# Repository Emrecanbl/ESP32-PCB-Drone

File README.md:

# Micro-Drone Flight Stack — STM32H743

A custom flight controller for a 3S micro-drone, designed from scratch: schematic, multi-layer PCB, and firmware.
The board is not a carrier for off-the-shelf modules — MCU, sensors, power tree and connectivity are all part of one design.

> **Status:** Rev 1 hardware design complete (KiCad 9). Firmware in development.

---

## 1. What this is

The goal is a **modular flight platform** that starts as a stabilised micro-drone and grows into an autonomous system: optical flow and ToF for indoor hold, GPS for outdoor navigation, and eventually a ROS 2 companion computer for SLAM.

Every stage is built and verified before the next one starts. This repository documents the hardware as designed and the firmware as it comes up.

**Why build the controller instead of using an off-the-shelf FC:** the interesting engineering is in the parts a commercial board hides — the analogue power path under a switching regulator, the sensor bus layout, the real-time task structure, and the failure behaviour when a link drops. Designing the board makes all of that visible and measurable.

---

## 2. Flight controller hardware (Rev 1)

### 2.1 Core

| Item | Part | Notes |
|---|---|---|
| MCU | **STM32H743VIT** | Cortex-M7, LQFP-100 |
| HSE crystal | 13.0625 MHz | with 10 pF load caps |
| LSE crystal | 32.768 kHz | RTC / low-speed domain |
| Debug | SWD/JTAG header (J2) | |
| Console | UART header (J3) | separate from the ESP32 link |
| USB | USB-C receptacle (J9) | USB 2.0 FS, CC1/CC2 with 5.1 kΩ sink resistors |

VCAP decoupling (2× 2.2 µF), bulk + local 100 nF per supply pin, and a **600 Ω ferrite on VDDA** to keep the ADC/analogue reference off the digital rail.

### 2.2 Sensors

| Function | Part | Bus | Notes |
|---|---|---|---|
| IMU | **Bosch BMI088** | SPI | separate accel/gyro dies, separate chip selects, 4 interrupt lines routed (2× accel, 2× gyro) |
| Barometer | **BMP280** | I²C | shared bus with magnetometer |
| Magnetometer | **MMC5983MA** | I²C | heading reference for yaw drift correction |
| ToF range | **VL53L1CXV0FY1** | I²C | altitude above ground, `XSHUT` + interrupt routed |
| Optical flow | **PMW3901MB-TXQT** | SPI | XY velocity estimation, dedicated RC-filtered supply (3 Ω + 100 nF/22 µF) and motion interrupt |

All sensors run from a **separately filtered +3.3VA rail** (ferrite from +3.3V), so switching noise from the regulators and the ESC lines does not land on the IMU supply. Interrupt-driven sampling is wired for both IMU dies rather than polling.

### 2.3 Power tree

```
Battery (3S) ──► ISL85005FRZ buck ──┬──► +5V ──► AP2112K-3.3 ──► +3.3V ──[FB 600Ω]──► +3.3VA (sensors)
                (3.3 µH / 5 A)      │
USB-C VBUS ─────[SB120]─────────────┘          +5V ──► LT1963A-1.8 ──► +1.8V (CAN transceiver I/O)
```

- **Schottky ORing (SB120)** between USB VBUS and the battery-derived 5 V, so the board can be powered and debugged over USB with the battery connected.
- **Buck first, LDO second:** the switching stage carries the current, the LDO cleans up the rail the MCU and sensors see. A single LDO from 3S would have to burn the whole difference as heat.
- Separate 1.8 V rail supplies the CAN transceiver's I/O reference.

### 2.4 Connectivity and expansion

| Interface | Detail |
|---|---|
| **ESC output (J1)** | 4× timer outputs to a 4-in-1 ESC (DShot) |
| **CAN (J5)** | MCP2562-E-MF transceiver, 120 Ω termination, `CAN_SLEEP` under MCU control |
| **ESP32-S3 socket (U7)** | XIAO ESP32-S3 DIP footprint on-board — UART + 4 GPIO, intended for camera / early vision experiments |
| **USB-C** | firmware update and host communication |

CAN is on the board deliberately: it is the bus this class of hardware talks to peripherals and companion boards with, and it makes the platform useful beyond a single airframe.

---

## 3. Gallery

<p align="center">

  <em>Flight controller</em>
</p>

---

## 4. Radio link and handheld transmitter

**Planned:** The RC link to an **nRF54L15** handheld unit using ESB / a proprietary 2.4 GHz protocol, for lower latency and better link budget control.

Whatever the radio, the failsafe requirement is the same: loss of link must put the aircraft into a defined state, not an undefined one.

---

## 5. Firmware

Target architecture on **FreeRTOS**, STM32 HAL/LL:

- Interrupt-driven IMU sampling, pre-filtering, rate and angle estimation
- Complementary / Madgwick attitude filter
- Cascaded PID control (rate → angle, plus vertical control)
- Sensor fusion: IMU + barometer + ToF + optical flow
- Custom motor mixer with a DShot backend
- Failsafe handling and arming state machine

Separate tasks for control, sensing, telemetry and link handling, with queues at the boundaries.

---

## 6. Status

| Module | Status |
|---|---|
| Flight controller schematic (Rev 1) | ✅ Complete |
| Flight controller PCB layout | ✅ Complete |
| Board fabrication / assembly | 🟡 In progress |
| ESP32-S3 handheld transmitter | ✅ Rev 1 built |
| IMU + barometer integration | 🟡 In progress |
| ToF + optical flow | 🟡 Partial |
| PID controllers | 🟡 In progress |
| Magnetometer integration | 🔜 Planned |
| CAN interface bring-up | 🔜 Planned |
| nRF54L15 radio migration | 🔜 Planned |
| GPS (u-blox M10Q) | 🔜 Planned |
| CM5 companion / ROS 2 | 🔜 Planned |

---

## 7. Roadmap

**GPS integration (u-blox M10Q)** — UART + 1PPS sync, outdoor hold, integration into the global state estimator.

**Obstacle detection and local planning** — 8–10× VL53L7 ToF sensors in a 360° ring, local 3D bubble mapping, reactive path planning with direction-dependent speed limiting.

**Companion computer (CM5 + ROS 2)** — high-level navigation, SLAM / visual odometry, object detection and landing markers, MAVLink-style link between FC and companion.

**Early vision experiments (ESP32-S3)** — feature tracking and visual flow on the on-board module, before adding the CM5.

---

## 8. Repository layout

```
PCB_Design/   KiCad 9 project — schematic, layout, exports
Photos/       Renders, schematic captures and layout views
```

---

## 9. Tooling

KiCad 9.0.3 · STM32CubeIDE / CMake · FreeRTOS · Git · JTAG/SWD, logic analyser, oscilloscope

---

## License

To be added once the firmware source is published.

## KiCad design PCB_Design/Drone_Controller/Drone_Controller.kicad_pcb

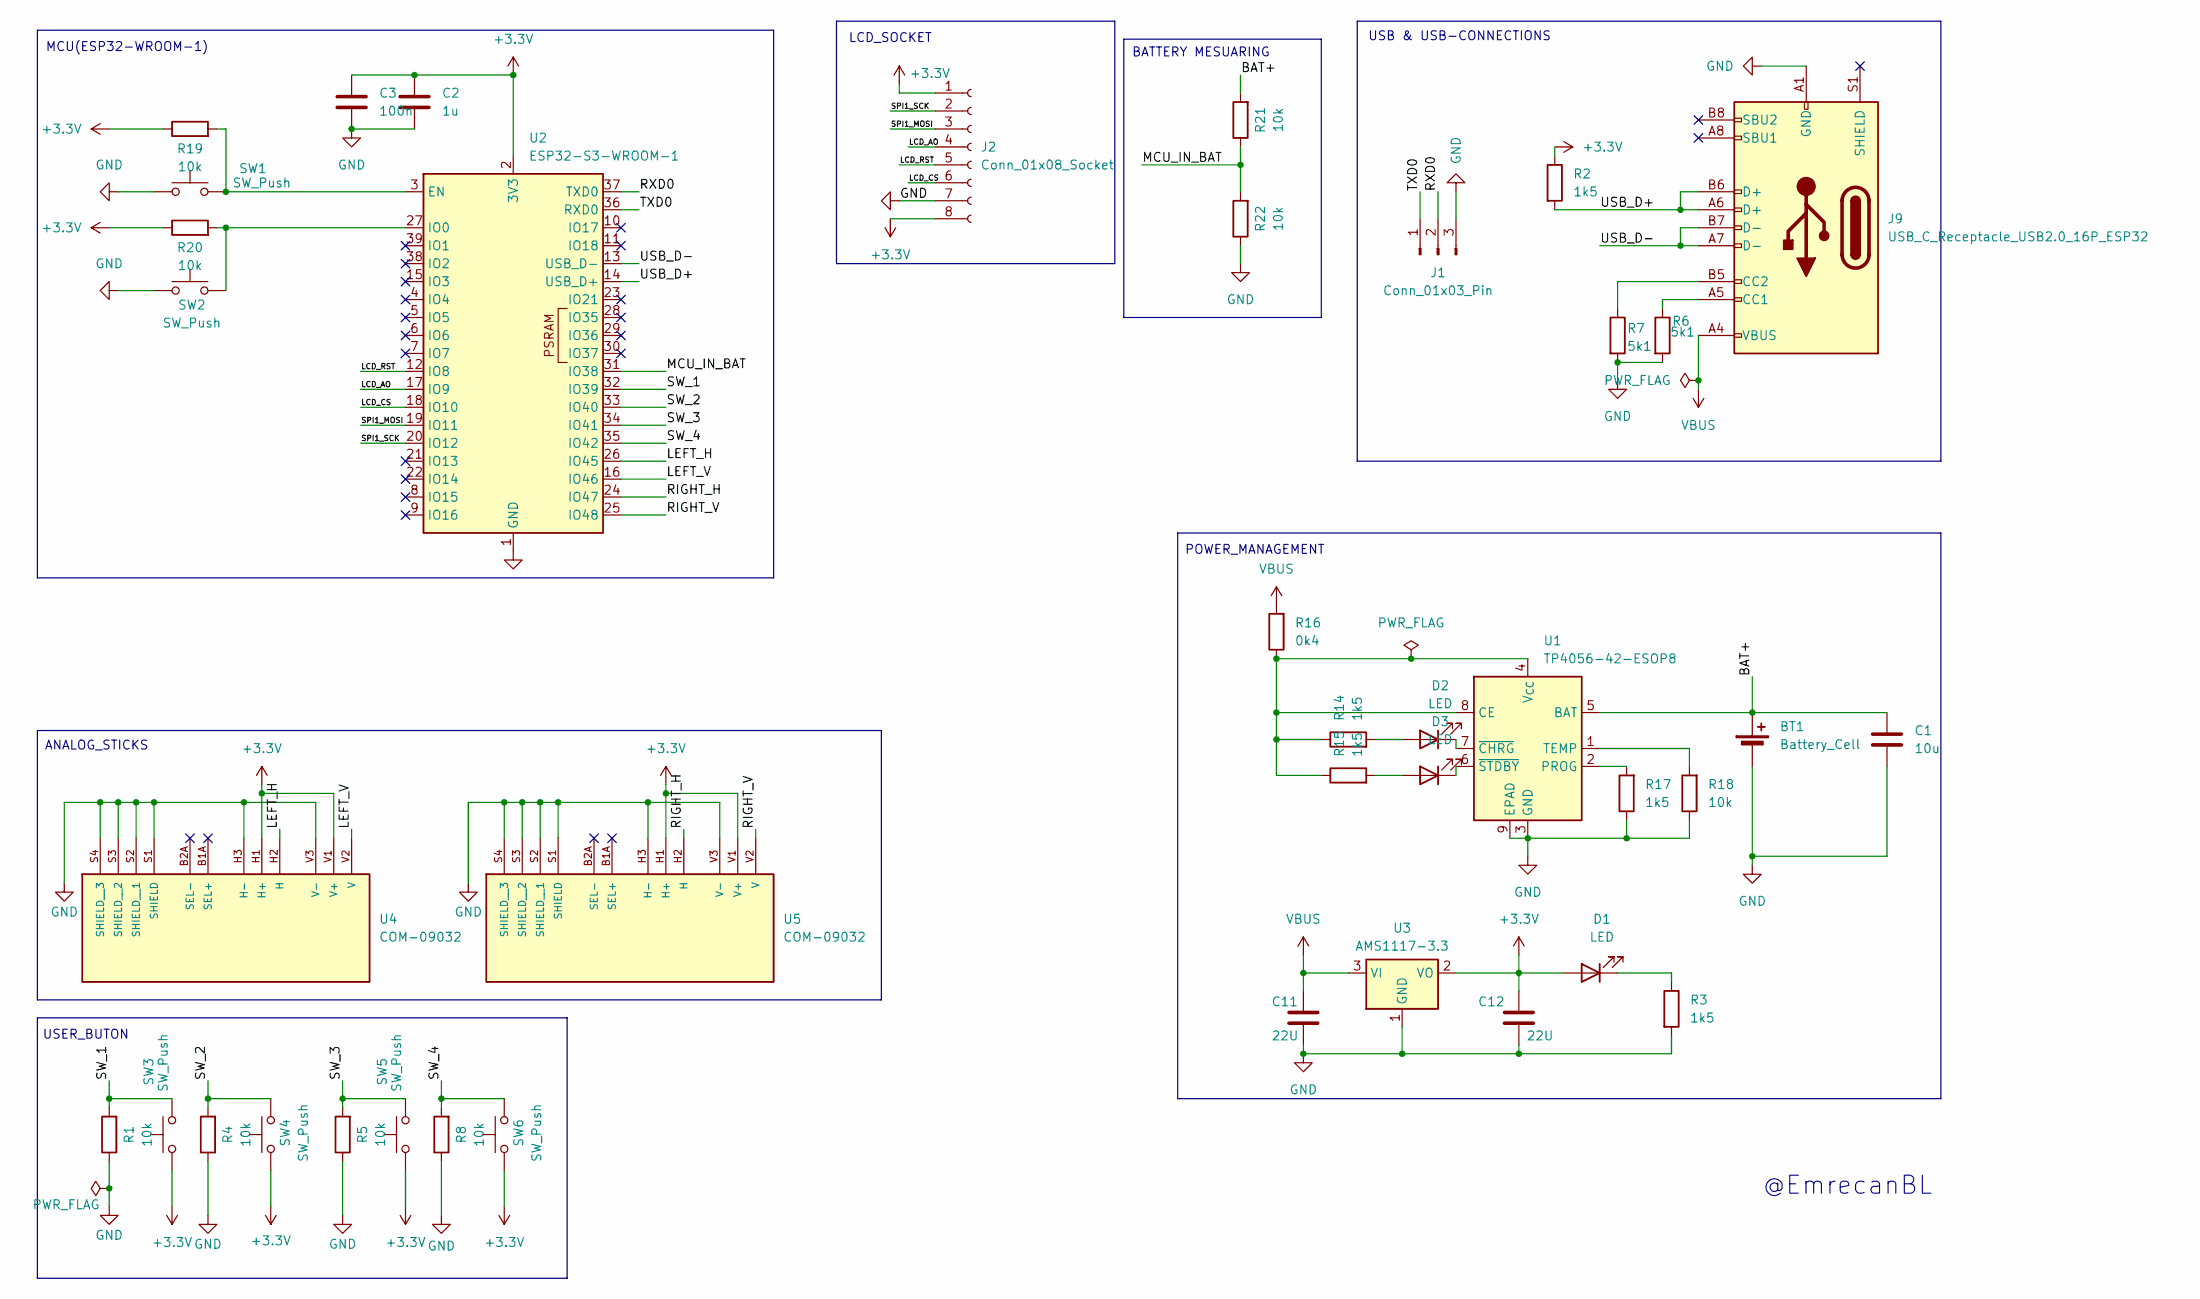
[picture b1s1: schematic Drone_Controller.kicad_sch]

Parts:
BT1: Battery_Cell; JST_PH_S2B-PH-SM4-TB_1x02-1MP_P2.00mm_Horizontal
C1: 10u; C_0402_1005Metric
C2: 1u; C_0402_1005Metric
C3: 100n; C_0402_1005Metric
C11, C12: 22U; C_0603_1608Metric
D1, D2, D3: LED; LED_0603_1608Metric
J1: Conn_01x03_Pin; PinHeader_1x03_P2.54mm_Vertical
J2: Conn_01x08_Socket; PinSocket_1x08_P2.54mm_Vertical
J9: USB_C_Receptacle_USB2.0_16P_ESP32; USB_C_Receptacle_GCT_USB4105-xx-A_16P_TopMnt_Horizontal
R1, R4, R5, R8, R18, R19, R20, R21, R22: 10k; R_0603_1608Metric
R2, R3, R14, R15, R17: 1k5; R_0603_1608Metric
R6, R7: 5k1; R_0603_1608Metric
R16: 0k4; R_0603_1608Metric
SW1, SW2, SW3, SW4, SW5, SW6: SW_Push; SW_PUSH_6mm_H4.3mm
U1: TP4056-42-ESOP8; SOIC-8-1EP_3.9x4.9mm_P1.27mm_EP2.41x3.3mm_ThermalVias
U2: ESP32-S3-WROOM-1
U3: AMS1117-3.3; SOT-223-3_TabPin2
U4, U5: COM-09032; Analog; PARTREV N/A

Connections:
+3.3V: C2.1, C3.1, C12.1, D1.2 (A), J2.1, J2.8, R2.1, R19.1, R20.1, SW3.1, SW4.1, SW5.1, SW6.1, U2.2 (3V3), U3.2 (VO), U4.H1 (H+), U4.V1 (V+), U5.H1 (H+), U5.V1 (V+)
/BAT+: BT1.1 (+), C1.1, R21.2, U1.5 (BAT)
/LCD_AO: J2.4, U2.17 (IO9)
/LCD_CS: J2.6, U2.18 (IO10)
/LCD_RST: J2.5, U2.12 (IO8)
/LEFT_H: U2.26 (IO45), U4.H2 (H)
/LEFT_V: U2.16 (IO46), U4.V2 (V)
/MCU_IN_BAT: R21.1, R22.2, U2.31 (IO38)
/RIGHT_H: U2.24 (IO47), U5.H2 (H)
/RIGHT_V: U2.25 (IO48), U5.V2 (V)
/RXD0: J1.2, U2.37 (TXD0)
/SPI1_MOSI: J2.3, U2.19 (IO11)
/SPI1_SCK: J2.2, U2.20 (IO12)
/SW_1: R1.2, SW3.2, U2.32 (IO39)
/SW_2: R4.2, SW4.2, U2.33 (IO40)
/SW_3: R5.2, SW5.2, U2.34 (IO41)
/SW_4: R8.2, SW6.2, U2.35 (IO42)
/TXD0: J1.1, U2.36 (RXD0)
/USB_D+: J9.A6 (D+), J9.B6 (D+), R2.2, U2.14 (USB_D+)
/USB_D-: J9.A7 (D-), J9.B7 (D-), U2.13 (USB_D-)
GND: BT1.2 (-), C1.2, C2.2, C3.2, C11.2, C12.2, J1.3, J2.7, J9.A1 (GND), J9.A12 (GND), J9.B1 (GND), J9.B12 (GND), R1.1, R3.2, R4.1, R5.1, R6.2, R7.2, R8.1, R17.1, R18.1, R22.1, SW1.1, SW2.1, U1.3 (GND), U1.9 (EPAD), U2.1 (GND), U2.40 (GND), U2.41 (GND), U3.1 (GND), U4.H3 (H-), U4.S1 (SHIELD), U4.S2 (SHIELD__1), U4.S3 (SHIELD__2), U4.S4 (SHIELD__3), U4.V3 (V-), U5.H3 (H-), U5.S1 (SHIELD), U5.S2 (SHIELD__1), U5.S3 (SHIELD__2), U5.S4 (SHIELD__3), U5.V3 (V-)
unnamed: D1.1 (K), R3.1
unnamed: D2.2 (A), R14.2
unnamed: D2.1 (K), U1.7 (~CHRG)
unnamed: D3.2 (A), R15.2
unnamed: D3.1 (K), U1.6 (~STDBY)
unnamed: J9.A5 (CC1), R6.1
unnamed: J9.B5 (CC2), R7.1
unnamed: R14.1, R15.1, R16.1, U1.4 (V_{CC}), U1.8 (CE)
unnamed: R17.2, U1.2 (PROG)
unnamed: R18.2, U1.1 (TEMP)
unnamed: R19.2, SW1.2, U2.3 (EN)
unnamed: R20.2, SW2.2, U2.27 (IO0)
VBUS: C11.1, J9.A4 (VBUS), J9.A9 (VBUS), J9.B4 (VBUS), J9.B9 (VBUS), R16.2, U3.3 (VI)

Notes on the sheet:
ANALOG_STICKS
MCU(ESP32-WROOM-1)
BATTERY MESUARING
USB & USB-CONNECTIONS
POWER_MANAGEMENT
LCD_SOCKET
USER_BUTON
@EmrecanBL

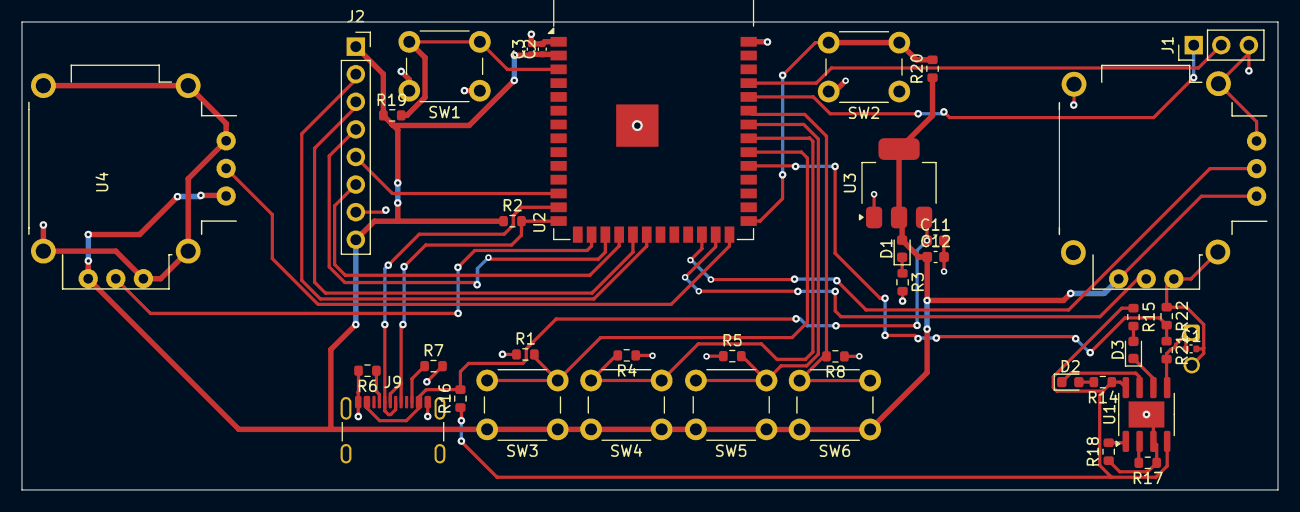
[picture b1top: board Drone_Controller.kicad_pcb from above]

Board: 2 copper layers, 115.7 x 43.1 mm, 40 parts (1 on the bottom side), 34 nets.

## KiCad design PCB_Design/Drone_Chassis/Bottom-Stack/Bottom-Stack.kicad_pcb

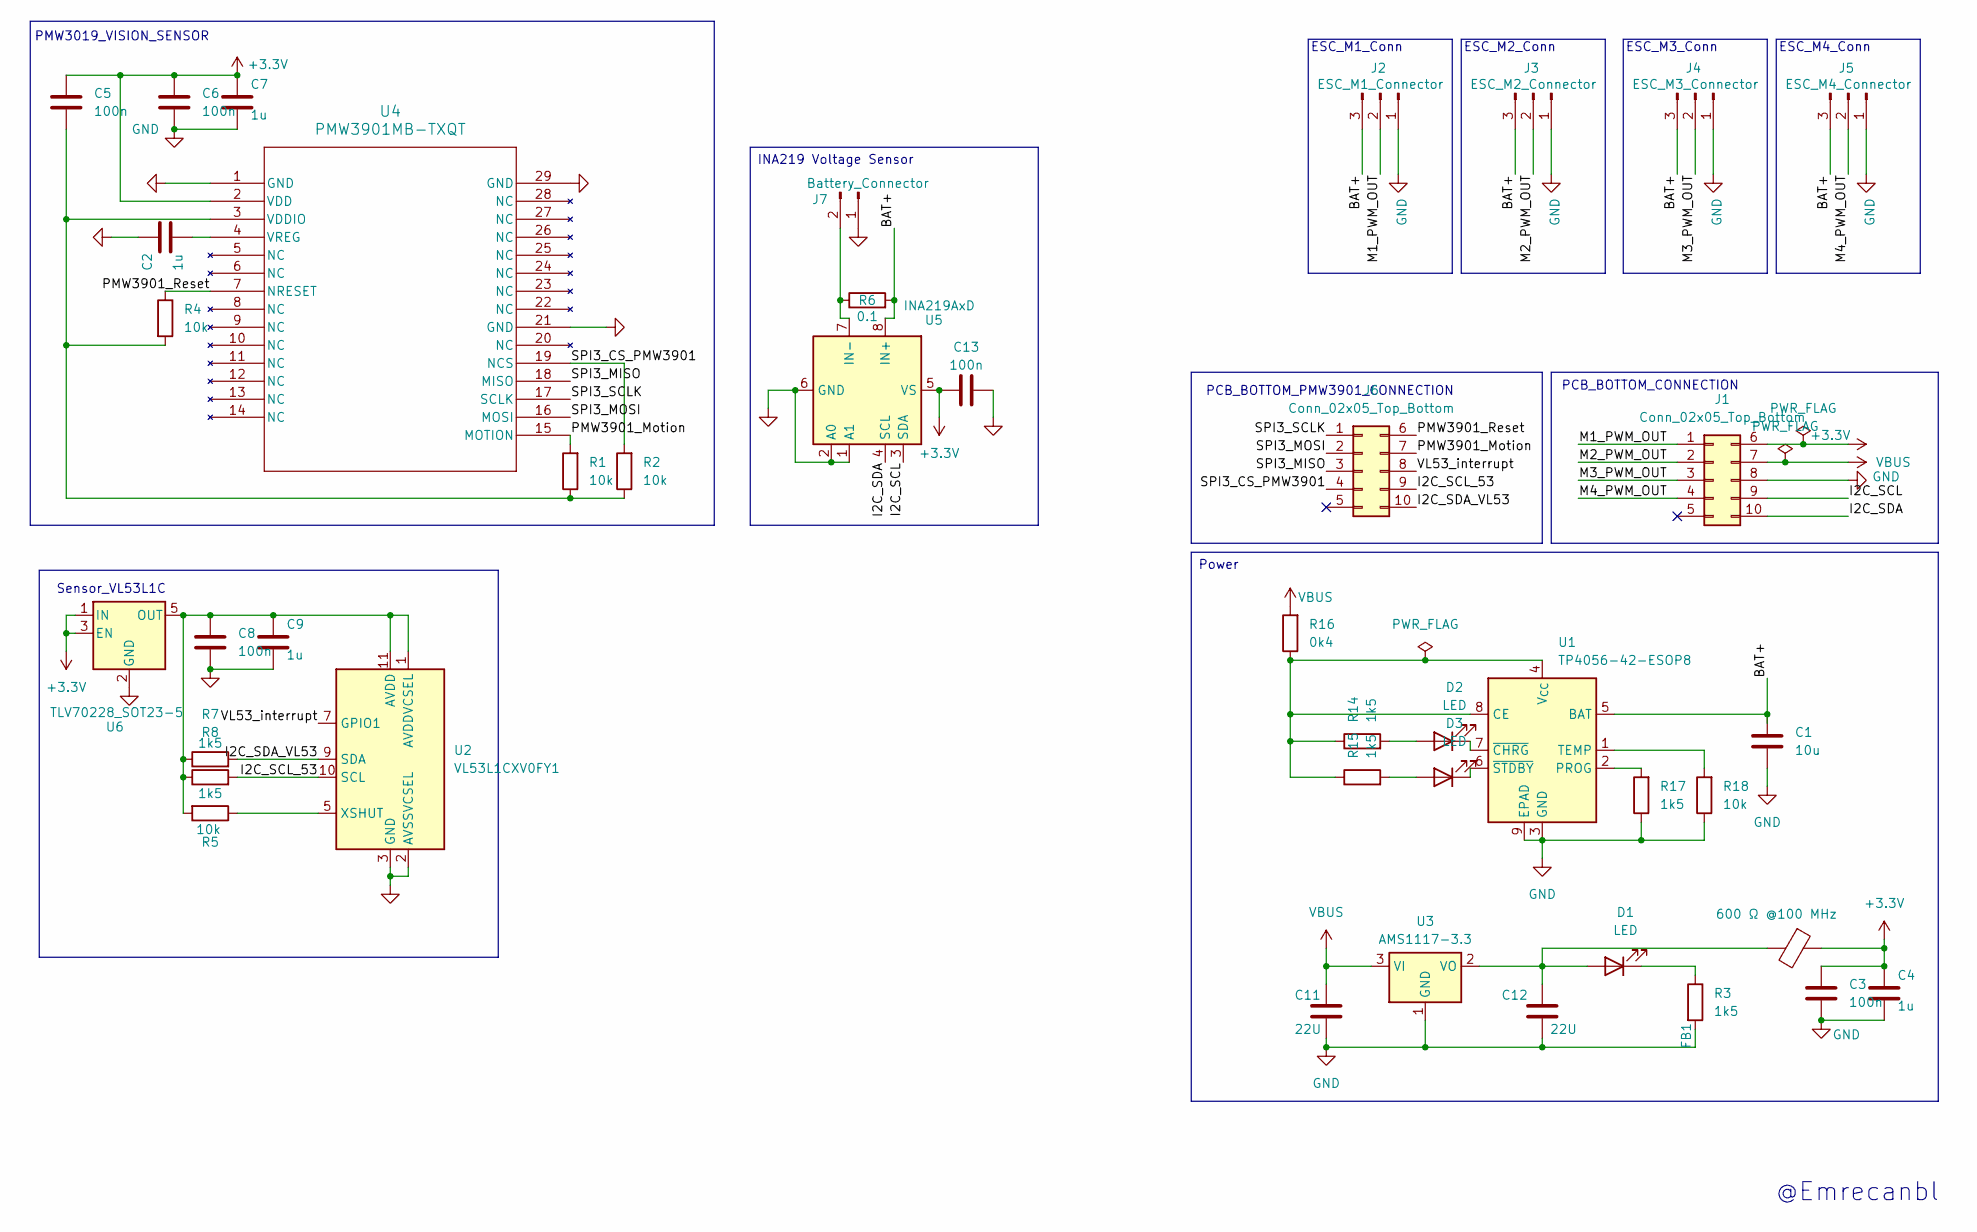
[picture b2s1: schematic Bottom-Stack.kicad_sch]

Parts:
C1: 10u; C_0402_1005Metric
C2, C4, C7, C9: 1u; C_0402_1005Metric
C3, C5, C6, C8, C13: 100n; C_0402_1005Metric
C11, C12: 22U; C_0603_1608Metric
D1, D2, D3: LED; LED_0603_1608Metric
FB1: 600 Ω @100 MHz; C_0201_0603Metric
J1, J6: Conn_02x05_Top_Bottom; PinHeader_2x05_P2.54mm_Vertical
J2: ESC_M1_Connector; SolderWire-0.1sqmm_1x03_P3.6mm_D0.4mm_OD1mm
J3: ESC_M2_Connector; SolderWire-0.1sqmm_1x03_P3.6mm_D0.4mm_OD1mm
J4: ESC_M3_Connector; SolderWire-0.1sqmm_1x03_P3.6mm_D0.4mm_OD1mm
J5: ESC_M4_Connector; SolderWire-0.1sqmm_1x03_P3.6mm_D0.4mm_OD1mm
J7: Battery_Connector; JST_PH_S2B-PH-SM4-TB_1x02-1MP_P2.00mm_Horizontal
R1, R2, R4, R5, R18: 10k; R_0603_1608Metric
R3, R7, R8, R14, R15, R17: 1k5; R_0603_1608Metric
R6: 0.1; R_0402_1005Metric
R16: 0k4; R_0603_1608Metric
U1: TP4056-42-ESOP8; SOIC-8-1EP_3.9x4.9mm_P1.27mm_EP2.41x3.3mm_ThermalVias
U2: VL53L1CXV0FY1; ST_VL53L1x
U3: AMS1117-3.3; SOT-223-3_TabPin2
U4: PMW3901MB-TXQT; QFN_01MB-TXQT_PIX
U5: INA219AxD; SOIC-8_3.9x4.9mm_P1.27mm
U6: TLV70228_SOT23-5; SOT-23-5

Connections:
+3.3V: C3.1, C4.1, C5.1, C6.1, C7.1, C13.1, FB1.1, J1.6, U4.2 (VDD), U5.5 (VS), U6.1 (IN), U6.3 (EN)
/BAT+: C1.1, J2.3, J3.3, J4.3, J5.3, R6.2, U1.5 (BAT), U5.8 (IN+)
/I2C_SCL: J1.9, U5.3 (SDA)
/I2C_SCL_53: J6.9, R8.2, U2.10 (SCL)
/I2C_SDA: J1.10, U5.4 (SCL)
/I2C_SDA_VL53: J6.10, R7.2, U2.9 (SDA)
/M1_PWM_OUT: J1.1, J2.2
/M2_PWM_OUT: J1.2, J3.2
/M3_PWM_OUT: J1.3, J4.2
/M4_PWM_OUT: J1.4, J5.2
/PMW3901_Motion: J6.7, R1.2, U4.15 (MOTION)
/PMW3901_Reset: J6.6, R4.1, U4.7 (NRESET)
/SPI3_CS_PMW3901: J6.4, R2.2, U4.19 (NCS)
/SPI3_MISO: J6.3, U4.18 (MISO)
/SPI3_MOSI: J6.2, U4.16 (MOSI)
/SPI3_SCLK: J6.1, U4.17 (SCLK)
/VL53_interrupt: J6.8, U2.7 (GPIO1)
GND: C1.2, C2.1, C3.2, C4.2, C6.2, C7.2, C8.2, C9.2, C11.2, C12.2, C13.2, J1.8, J2.1, J3.1, J4.1, J5.1, J7.1, R3.2, R17.1, R18.1, U1.3 (GND), U1.9 (EPAD), U2.2 (AVSSVCSEL), U2.3 (GND), U2.4 (GND), U2.6 (GND), U2.12 (GND), U3.1 (GND), U4.1 (GND), U4.21 (GND), U4.29 (GND), U5.1 (A1), U5.2 (A0), U5.6 (GND), U6.2 (GND)
unnamed: C12.1, D1.2 (A), FB1.2, U3.2 (VO)
unnamed: D1.1 (K), R3.1
unnamed: D2.2 (A), R14.2
unnamed: D2.1 (K), U1.7 (~CHRG)
unnamed: D3.2 (A), R15.2
unnamed: D3.1 (K), U1.6 (~STDBY)
unnamed: J7.2, R6.1, U5.7 (IN-)
unnamed: R14.1, R15.1, R16.1, U1.4 (V_{CC}), U1.8 (CE)
unnamed: R17.2, U1.2 (PROG)
unnamed: R18.2, U1.1 (TEMP)
unnamed: C8.1, C9.1, R5.2, R7.1, R8.1, U2.1 (AVDDVCSEL), U2.11 (AVDD), U6.5 (OUT)
unnamed: R5.1, U2.5 (XSHUT)
unnamed: C5.2, R1.1, R2.1, R4.2, U4.3 (VDDIO)
unnamed: C2.2, U4.4 (VREG)
VBUS: C11.1, J1.7, R16.2, U3.3 (VI)

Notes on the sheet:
PCB_BOTTOM_PMW3901_CONNECTION
PCB_BOTTOM_CONNECTION
@Emrecanbl
ESC_M2_Conn
PMW3019_VISION_SENSOR
ESC_M1_Conn
ESC_M3_Conn
Sensor_VL53L1C
ESC_M4_Conn
Power
INA219 Voltage Sensor

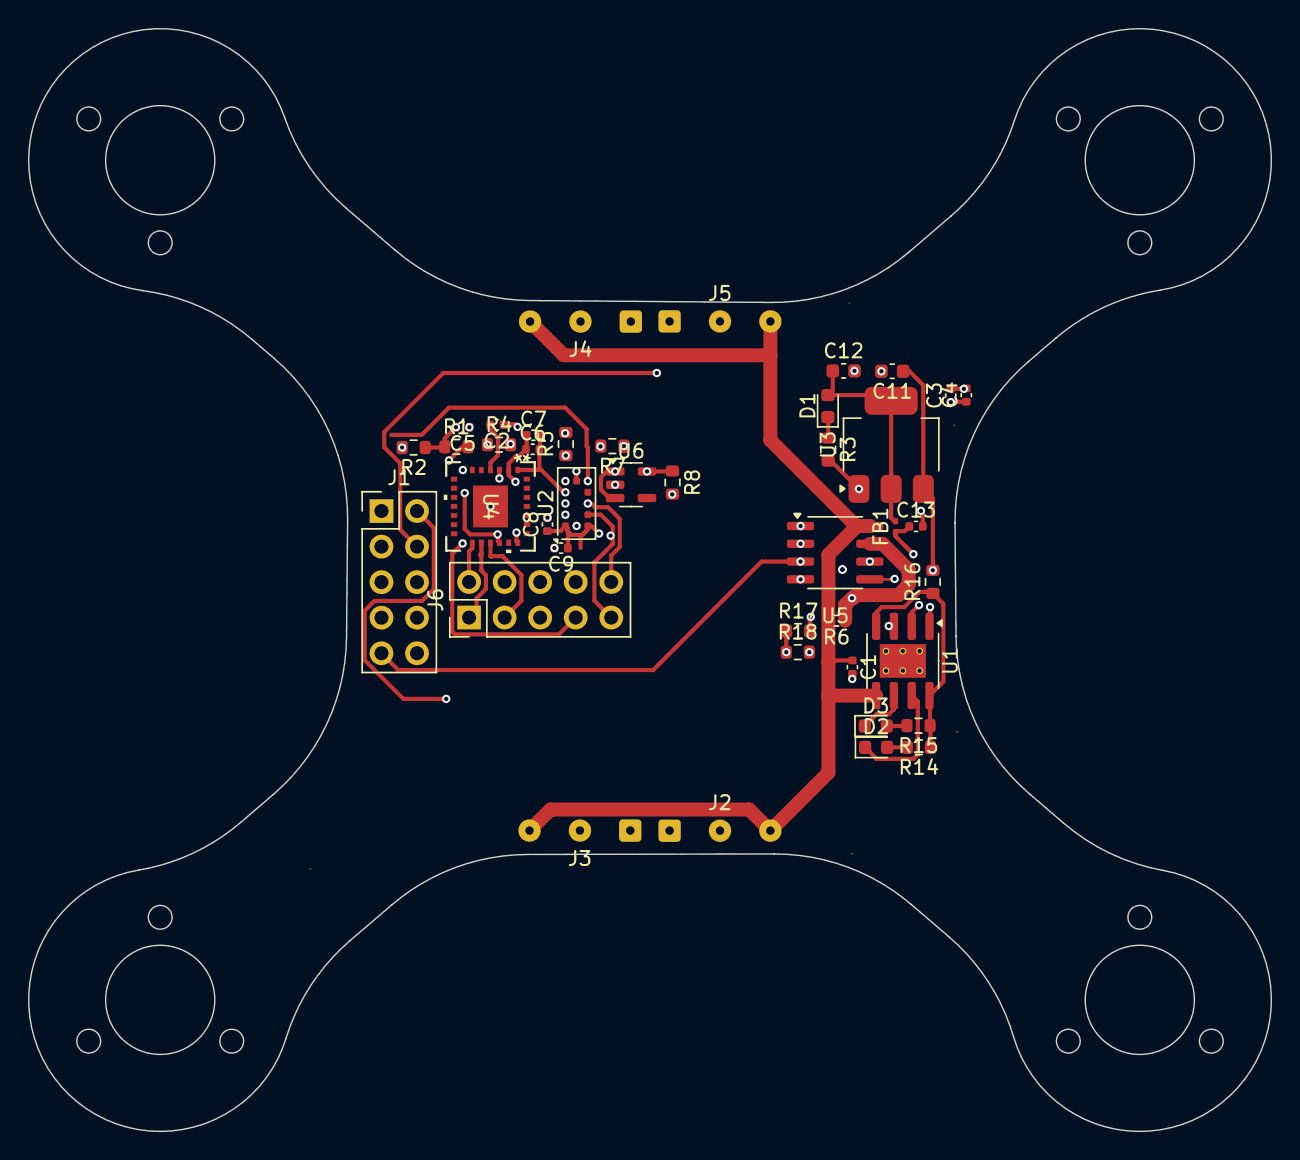
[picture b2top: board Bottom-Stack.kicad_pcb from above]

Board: 4 copper layers, 88.8 x 78.8 mm, 42 parts (1 on the bottom side), 33 nets.

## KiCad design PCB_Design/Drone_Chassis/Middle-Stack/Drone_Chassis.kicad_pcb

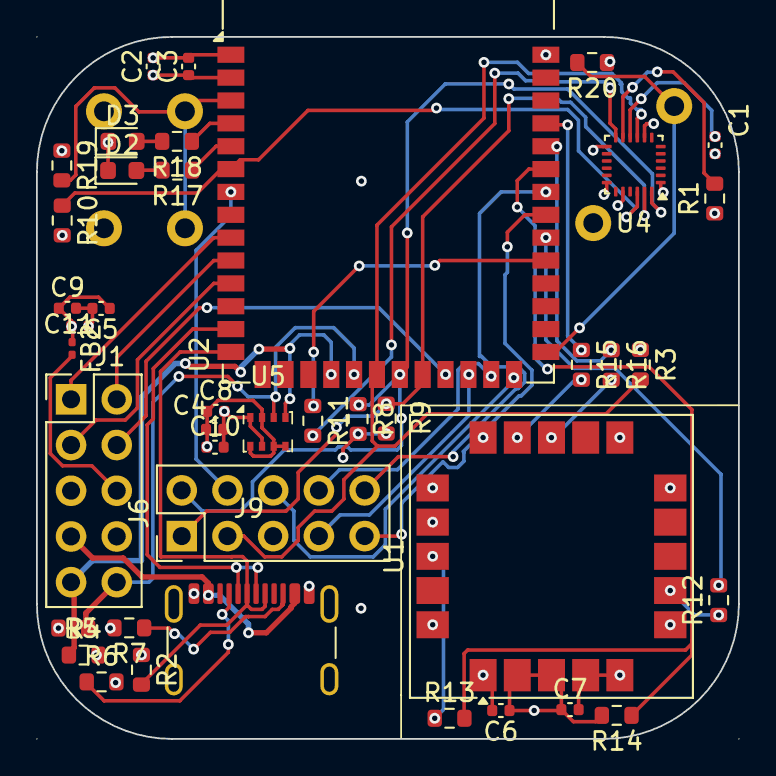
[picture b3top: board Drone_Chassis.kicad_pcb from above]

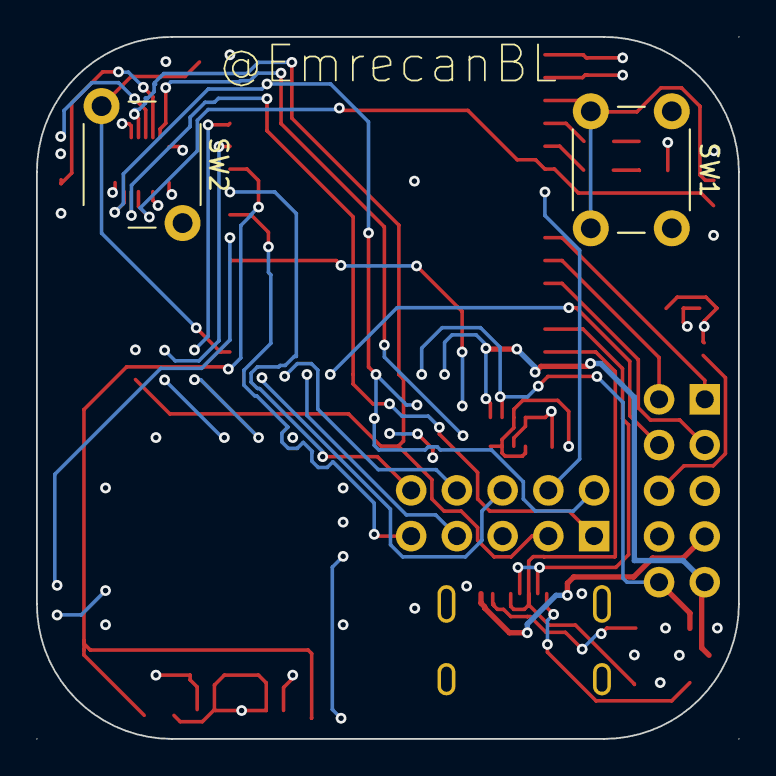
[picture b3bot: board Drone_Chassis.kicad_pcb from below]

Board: 4 copper layers, 39.0 x 39.0 mm, 43 parts (2 on the bottom side), 42 nets.

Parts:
C1, C3, C4, C6, C8, C10: 100n; C_0402_1005Metric
C2, C7, C9: 1u; C_0402_1005Metric
C5: 10n; C_0402_1005Metric
C11: 10u; C_0402_1005Metric
D2, D3: LED; LED_0603_1608Metric
FB2: 600 Ω @100 MHz; C_0201_0603Metric
J1, J6: Conn_02x05_Top_Bottom; PinHeader_2x05_P2.54mm_Vertical
J9: USB_C_Receptacle_USB2.0_16P_ESP32; USB_C_Receptacle_GCT_USB4105-xx-A_16P_TopMnt_Horizontal
R1, R3, R8, R9, R10, R14, R19, R20: 10k; R_0603_1608Metric
R2, R4, R5, R17, R18: 1k5; R_0603_1608Metric
R6, R7: 5k1; R_0603_1608Metric
R11, R12, R13, R15, R16: 0k1; R_0603_1608Metric
SW1, SW2: SW_Push; SW_PUSH_6mm_H4.3mm
U1: SAM-M10Q; ublox_SAM-M8Q
U2: ESP32-S3-WROOM-1
U4: MPU-9250; InvenSense_QFN-24_3x3mm_P0.4mm
U5: BMP280; Bosch_LGA-8_2x2.5mm_P0.65mm_ClockwisePinNumbering

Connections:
+3.3V: C2.1, C3.1, C4.1, C5.1, C6.1, C7.1, C8.1, C9.1, C10.1, C11.1, FB2.1, R2.1, R4.2, R5.2, R8.2, R9.2, R10.2, R14.2, R19.1, R20.1, U1.2 (VCC_IO), U1.3 (V_BCKP), U1.17 (VCC), U2.2 (3V3), U4.1 (RESV_VDDIO), U4.8 (VDDIO), U4.13 (VDD), U5.2 (CSB), U5.5 (SDO), U5.6 (VDDIO), U5.8 (VDD)
/I2C_SCL: J1.9, R4.1, U2.18 (IO10), U5.4 (SCK)
/I2C_SCL_53: J6.9, U2.33 (IO40)
/I2C_SDA: J1.10, R5.1, U2.19 (IO11), U5.3 (SDI)
/I2C_SDA_VL53: J6.10, U2.34 (IO41)
/M1_PWM_OUT: J1.1, U2.9 (IO16)
/M2_PWM_OUT: J1.2, U2.10 (IO17)
/M3_PWM_OUT: J1.3, U2.11 (IO18)
/M4_PWM_OUT: J1.4, U2.23 (IO21)
/MPU-9250_INIT: R11.1, U2.31 (IO38)
/PMW3901_Motion: J6.7, U2.24 (IO47)
/PMW3901_Reset: J6.6, U2.26 (IO45)
/RESET_N: R13.2, R14.1, U2.35 (IO42)
/RXD0: R16.1, U2.36 (RXD0)
/SPI3_CS_MPU-9250: R10.1, U2.6 (IO6), U4.22 (~CS)
/SPI3_CS_PMW3901: J6.4, U2.7 (IO7)
/SPI3_MISO: J6.3, R3.2, U2.20 (IO12), U4.9 (AD0/MISO)
/SPI3_MOSI: J6.2, R8.1, U2.21 (IO13), U4.24 (SDA/MOSI)
/SPI3_SCLK: J6.1, R9.1, U2.22 (IO14), U4.23 (SCL/SCLK)
/TIMEPULSE: R12.2, U2.32 (IO39)
/TXD0: R15.1, U2.37 (TXD0)
/USB_D+: J9.A6 (D+), J9.B6 (D+), R2.2, U2.14 (USB_D+)
/USB_D-: J9.A7 (D-), J9.B7 (D-), U2.13 (USB_D-)
/VL53_interrupt: J6.8, U2.25 (IO48)
GND: C1.2, C2.2, C3.2, C4.2, C5.2, C6.2, C7.2, C8.2, C9.2, C10.2, C11.2, D2.1 (K), D3.1 (K), J1.8, J9.A1 (GND), J9.A12 (GND), J9.B1 (GND), J9.B12 (GND), J9.S1 (SHIELD), R1.1, R3.1, R6.2, R7.2, SW1.1, SW2.1, U1.1 (GND), U1.4 (GND), U1.5 (GND), U1.6 (GND), U1.10 (GND), U1.11 (GND), U1.15 (GND), U1.16 (GND), U1.20 (GND), U2.1 (GND), U2.40 (GND), U4.18 (GND), U4.20 (RESV_GND), U5.1 (GND), U5.7 (GND)
unnamed: D2.2 (A), R17.2
unnamed: D3.2 (A), R18.2
unnamed: FB2.2, J1.6
unnamed: J9.A5 (CC1), R6.1
unnamed: J9.B5 (CC2), R7.1
unnamed: R15.2, U1.14 (RXD)
unnamed: R12.1, U1.7 (TIMEPULSE)
unnamed: R16.2, U1.13 (TXD)
unnamed: R13.1, U1.18 (~RESET)
unnamed: R19.2, SW1.2, U2.3 (EN)
unnamed: R20.2, SW2.2, U2.27 (IO0)
unnamed: R18.1, U2.4 (IO4)
unnamed: R17.1, U2.5 (IO5)
unnamed: R1.2, U4.11 (FSYNC)
unnamed: R11.2, U4.12 (INT)
unnamed: C1.1, U4.10 (REGOUT)
VBUS: J1.7, J9.A4 (VBUS), J9.A9 (VBUS), J9.B4 (VBUS), J9.B9 (VBUS)

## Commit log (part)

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2025-11-06 Create New Project
2025-11-06 FC_Desing_Start
2025-11-07 PCB_Update
2025-11-09 PCB_V1_Final
2025-11-09 Update README with PCB renders
2025-11-29 Revise README for STM32H7 Micro-Drone Project
    Updated the README to reflect the transition from an ESP32-S3 based micro-drone to a STM32H7 flight stack, including new phases and features.
2025-11-29 Add gallery section to README
    Added a gallery section with images of PCB models and schematics.
2025-11-29 Add section for GPS Integration in README
